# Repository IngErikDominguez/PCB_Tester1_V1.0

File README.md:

# PCB_Tester1_V1.0
Primer PCB del proyecto de tester, con la etapa de control con arduino pantalla OLED y control por medio de stick.

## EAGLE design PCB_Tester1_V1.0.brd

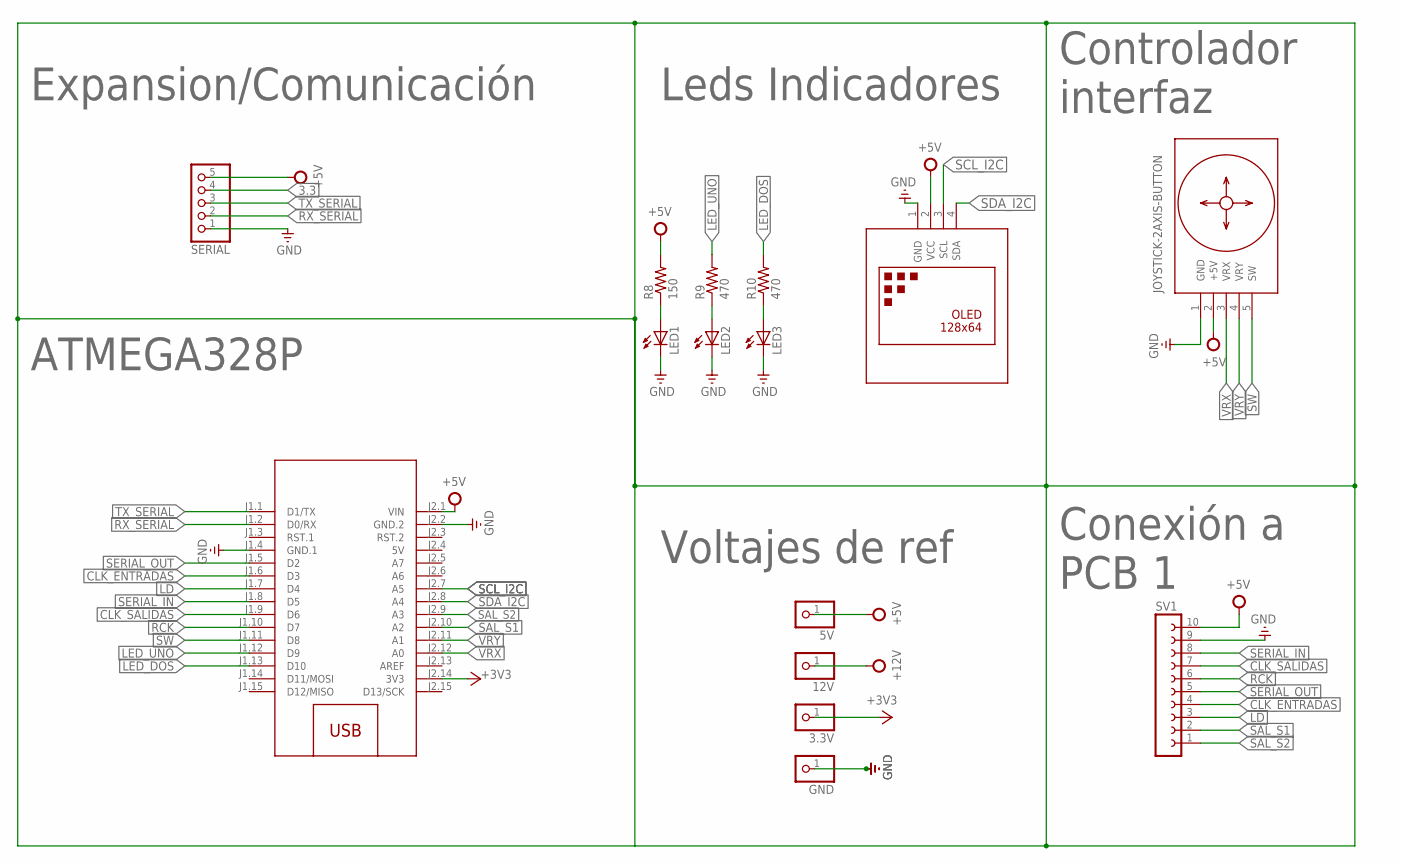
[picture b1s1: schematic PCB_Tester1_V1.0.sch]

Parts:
3.3V, 5V, 12V: PINHD-1X1; 1X01
GND: PINHD-1X1; 1X01
LED1, LED2, LED3: LED5MM
M2: ARDUINO-NANO-3.0
R8: 150; 0207/7
R9, R10: 470; 0207/7
SERIAL: PINHD-1X5; 1X05
SV1: FE10-1; FE10
U$2: DISPLAY-OLED-128X64-I2C
U$3: JOYSTICK-2AXIS-BUTTON

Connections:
3.3: SERIAL.4
5V: M2.J2.4 (5V)
+3V3: 3.3V.1, M2.J2.14 (3V3)
+5V: 5V.1, M2.J2.1 (VIN), R8.2, SERIAL.5, SV1.10, U$2.2 (VCC), U$3.2 (+5V)
+12V: 12V.1
CLK_ENTRADAS: M2.J1.6 (D3), SV1.4
CLK_SALIDAS: M2.J1.9 (D6), SV1.7
GND: GND.1, LED1.K (C), LED2.K (C), LED3.K (C), M2.J1.4 (GND.1), M2.J2.2 (GND.2), SERIAL.1, SV1.9, U$2.1 (GND), U$3.1 (GND)
LD: M2.J1.7 (D4), SV1.3
LED_DOS: M2.J1.13 (D10), R10.2
LED_UNO: M2.J1.12 (D9), R9.2
unnamed: LED1.A, R8.1
unnamed: LED2.A, R9.1
unnamed: LED3.A, R10.1
RCK: M2.J1.10 (D7), SV1.6
RX_SERIAL: M2.J1.2 (D0/RX), SERIAL.2
SAL_S1: M2.J2.10 (A2), SV1.2
SAL_S2: M2.J2.9 (A3), SV1.1
SCL_I2C: M2.J2.7 (A5), U$2.3 (SCL)
SDA_I2C: M2.J2.8 (A4), U$2.4 (SDA)
SERIAL_IN: M2.J1.8 (D5), SV1.8
SERIAL_OUT: M2.J1.5 (D2), SV1.5
SW: M2.J1.11 (D8), U$3.5 (SW)
TX_SERIAL: M2.J1.1 (D1/TX), SERIAL.3
VRX: M2.J2.12 (A0), U$3.3 (VRX)
VRY: M2.J2.11 (A1), U$3.4 (VRY)

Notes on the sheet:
ATMEGA328P
Leds Indicadores
Voltajes de ref
Expansion/Comunicación
Controlador interfaz
Conexión a PCB 1

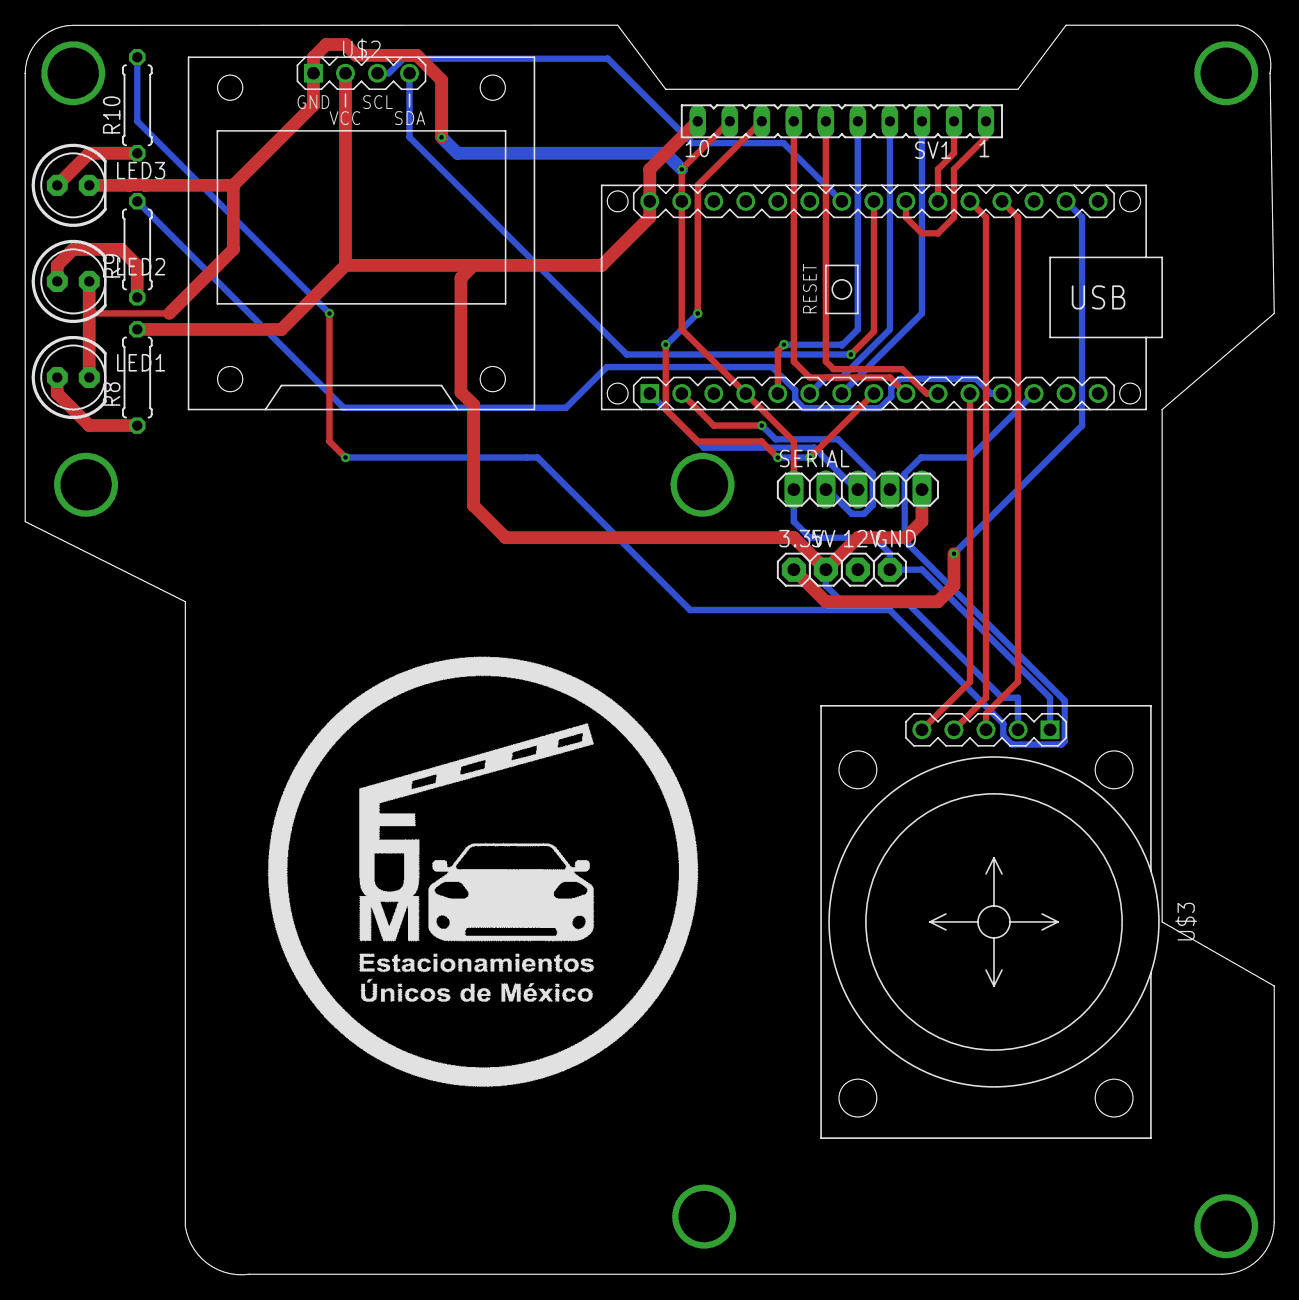
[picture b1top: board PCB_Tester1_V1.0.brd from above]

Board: 2 copper layers, 99.1 x 99.1 mm, 15 parts (0 on the bottom side), 23 nets.

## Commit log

2019-03-08 V1.0
    Añadida la capa de máscara

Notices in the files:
parts and their libraries:
diy-modules: Released under the Creative Commons Attribution 4.0 International License: http://creativecommons.org/licenses/by/4.0
